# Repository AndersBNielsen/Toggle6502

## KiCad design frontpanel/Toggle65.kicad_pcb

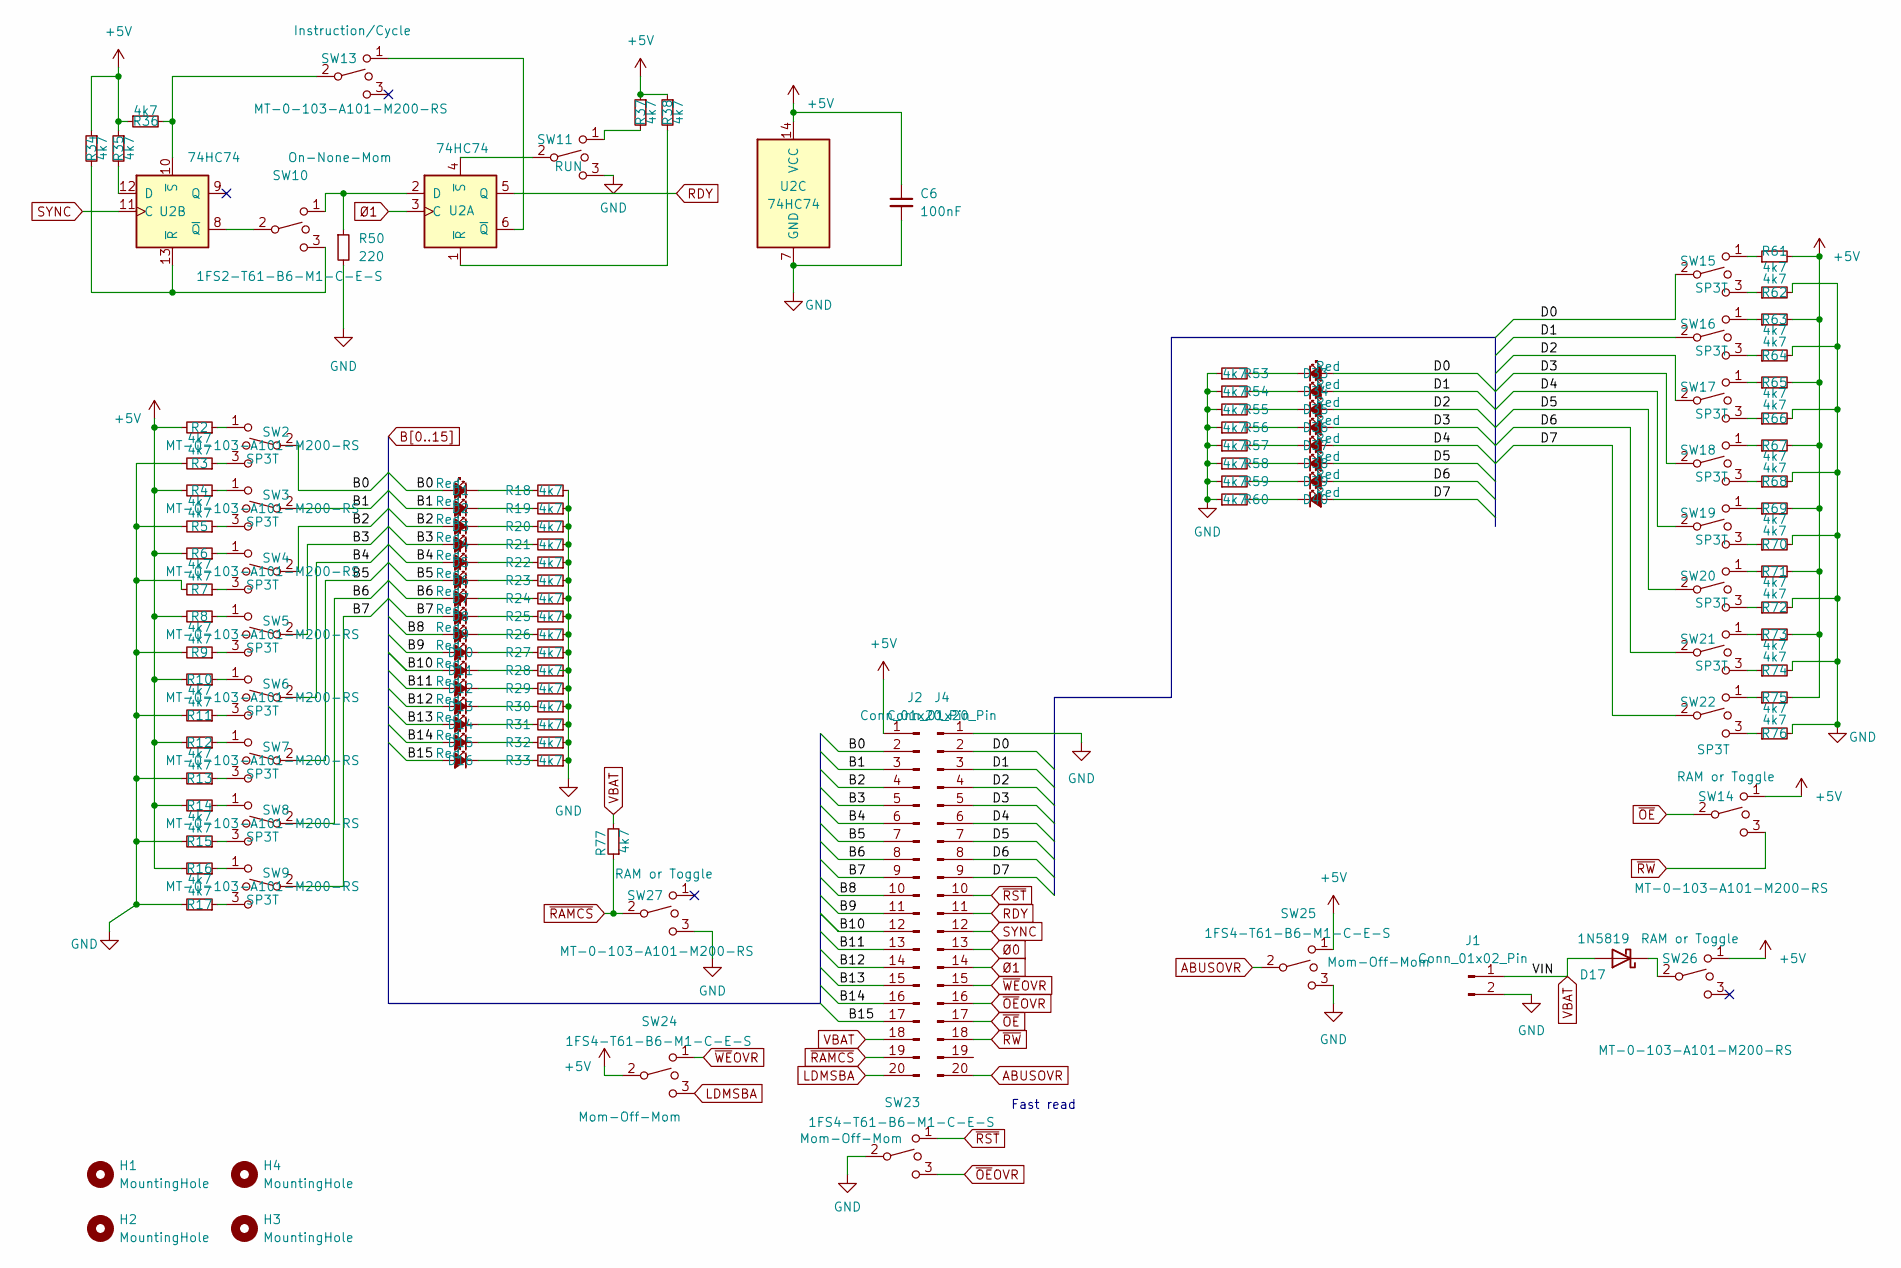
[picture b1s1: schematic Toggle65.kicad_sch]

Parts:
C6: 100nF; C_Disc_D5.0mm_W2.5mm_P5.00mm; LCSC C49678
D1, D2, D3, D4, D5, D6, D7, D8, D9, D10, D11, D12, D13, D14, D15, D16, D33, D34, D35, D36, D37, D38, D39, D40: Red; LED_D5.0mm
D17: 1N5819; D_DO-41_SOD81_P10.16mm_Horizontal
H1, H2, H3, H4: MountingHole; MountingHole_3.2mm_M3_DIN965
J1: Conn_01x02_Pin; PinHeader_1x02_P2.54mm_Vertical
J2, J4: Conn_01x20_Pin; PinHeader_1x20_P2.54mm_Vertical
R2, R3, R4, R5, R6, R7, R8, R9, R10, R11, R12, R13, R14, R15, R16, R17, R18, R19, R20, R21, R22, R23, R24, R25, R26, R27, R28, R29, R30, R31, R32, R33, R34, R35, R36, R37, R38, R53, R54, R55, R56, R57, R58, R59, R60, R61, R62, R63, R64, R65, R66, R67, R68, R69, R70, R71, R72, R73, R74, R75, R76, R77: 4k7; R_Axial_DIN0204_L3.6mm_D1.6mm_P5.08mm_Horizontal
R50: 220; R_Axial_DIN0204_L3.6mm_D1.6mm_P5.08mm_Horizontal
SW2, SW3, SW4, SW5, SW6, SW7, SW8, SW9, SW15, SW16, SW17, SW18, SW19, SW20, SW21, SW22: SP3T; SW_Toggle_Blue_wSlots; LCSC C1788493
SW10: On-None-Mom; SW_Toggle_Blue_wSlots
SW11: RUN; SW_Toggle_Blue_wSlots; LCSC C1788493
SW13: Instruction/Cycle; SW_Toggle_Blue_wSlots; LCSC C1788493
SW14, SW26, SW27: RAM or Toggle; SW_Toggle_Blue_wSlots; LCSC C1788493
SW23, SW24, SW25: Mom-Off-Mom; SW_Toggle_Blue_wSlots
U2: 74HC74; DIP-14_W7.62mm_Socket

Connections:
+5V: C6.1, J2.1, R2.2, R4.2, R6.2, R8.2, R10.2, R12.2, R14.2, R16.2, R34.1, R35.1, R36.1, R37.1, R38.1, R61.2, R63.2, R65.2, R67.2, R69.2, R71.2, R73.2, R75.2, SW14.1, SW24.2, SW25.1, SW26.1, U2.14 (VCC)
/D0: D33.2 (A), J4.2, SW15.2
/D1: D34.2 (A), J4.3, SW16.2
/D2: D35.2 (A), J4.4, SW17.2
/D3: D36.2 (A), J4.5, SW18.2
/D4: D37.2 (A), J4.6, SW19.2
/D5: D38.2 (A), J4.7, SW20.2
/D6: D39.2 (A), J4.8, SW21.2
/D7: D40.2 (A), J4.9, SW22.2
ABUSOVR: J4.20, SW25.2
B0: D1.2 (A), J2.2, SW2.2
B1: D2.2 (A), J2.3, SW3.2
B2: D3.2 (A), J2.4, SW4.2
B3: D4.2 (A), J2.5, SW5.2
B4: D5.2 (A), J2.6, SW6.2
B5: D6.2 (A), J2.7, SW7.2
B6: D7.2 (A), J2.8, SW8.2
B7: D8.2 (A), J2.9, SW9.2
B8: D9.2 (A), J2.10
B9: D10.2 (A), J2.11
B10: D11.2 (A), J2.12
B11: D12.2 (A), J2.13
B12: D13.2 (A), J2.14
B13: D14.2 (A), J2.15
B14: D15.2 (A), J2.16
B15: D16.2 (A), J2.17
GND: C6.2, J1.2, J4.1, R3.2, R5.2, R7.2, R9.2, R11.2, R13.2, R15.2, R17.2, R18.1, R19.1, R20.1, R21.1, R22.1, R23.1, R24.1, R25.1, R26.1, R27.1, R28.1, R29.1, R30.1, R31.1, R32.1, R33.1, R50.2, R53.1, R54.1, R55.1, R56.1, R57.1, R58.1, R59.1, R60.1, R62.2, R64.2, R66.2, R68.2, R70.2, R72.2, R74.2, R76.2, SW11.3, SW23.2, SW25.3, SW27.3, U2.7 (GND)
LDMSBA: J2.20, SW24.3
unnamed: D1.1 (K), R18.2
unnamed: D2.1 (K), R19.2
unnamed: D3.1 (K), R20.2
unnamed: D4.1 (K), R21.2
unnamed: D5.1 (K), R22.2
unnamed: D6.1 (K), R23.2
unnamed: D7.1 (K), R24.2
unnamed: D8.1 (K), R25.2
unnamed: D9.1 (K), R26.2
unnamed: D10.1 (K), R27.2
unnamed: D11.1 (K), R28.2
unnamed: D12.1 (K), R29.2
unnamed: D13.1 (K), R30.2
unnamed: D14.1 (K), R31.2
unnamed: D15.1 (K), R32.2
unnamed: D16.1 (K), R33.2
unnamed: D17.1 (K), SW26.2
unnamed: D33.1 (K), R53.2
unnamed: D34.1 (K), R54.2
unnamed: D35.1 (K), R55.2
unnamed: D36.1 (K), R56.2
unnamed: D37.1 (K), R57.2
unnamed: D38.1 (K), R58.2
unnamed: D39.1 (K), R59.2
unnamed: D40.1 (K), R60.2
unnamed: R2.1, SW2.1
unnamed: R3.1, SW2.3
unnamed: R4.1, SW3.1
unnamed: R5.1, SW3.3
unnamed: R6.1, SW4.1
unnamed: R7.1, SW4.3
unnamed: R8.1, SW5.1
unnamed: R9.1, SW5.3
unnamed: R10.1, SW6.1
unnamed: R11.1, SW6.3
unnamed: R12.1, SW7.1
unnamed: R13.1, SW7.3
unnamed: R14.1, SW8.1
unnamed: R15.1, SW8.3
unnamed: R16.1, SW9.1
unnamed: R17.1, SW9.3
unnamed: R37.2, SW11.1
unnamed: R61.1, SW15.1
unnamed: R62.1, SW15.3
unnamed: R63.1, SW16.1
unnamed: R64.1, SW16.3
unnamed: R65.1, SW17.1
unnamed: R66.1, SW17.3
unnamed: R67.1, SW18.1
unnamed: R68.1, SW18.3
unnamed: R69.1, SW19.1
unnamed: R70.1, SW19.3
unnamed: R71.1, SW20.1
unnamed: R72.1, SW20.3
unnamed: R73.1, SW21.1
unnamed: R74.1, SW21.3
unnamed: R75.1, SW22.1
unnamed: R76.1, SW22.3
unnamed: R50.1, SW10.1, U2.2 (D)
unnamed: SW13.1, U2.6 (~Q)
unnamed: R38.2, U2.1 (~R)
unnamed: SW11.2, U2.4 (~S)
unnamed: R35.2, U2.12 (D)
unnamed: SW10.2, U2.8 (~Q)
unnamed: R34.2, SW10.3, U2.13 (~R)
unnamed: R36.2, SW13.2, U2.10 (~S)
RDY: J4.11, U2.5 (Q)
SYNC: J4.12, U2.11 (C)
VBAT: D17.2 (A), J1.1, J2.18, R77.2
~OE: J4.17, SW14.2
~OEOVR: J4.16, SW23.3
~RAMCS: J2.19, R77.1, SW27.2
~RST: J4.10, SW23.1
~RW: J4.18, SW14.3
~WEOVR: J4.15, SW24.1
Ø0: J4.13
Ø1: J4.14, U2.3 (C)

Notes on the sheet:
Fast read

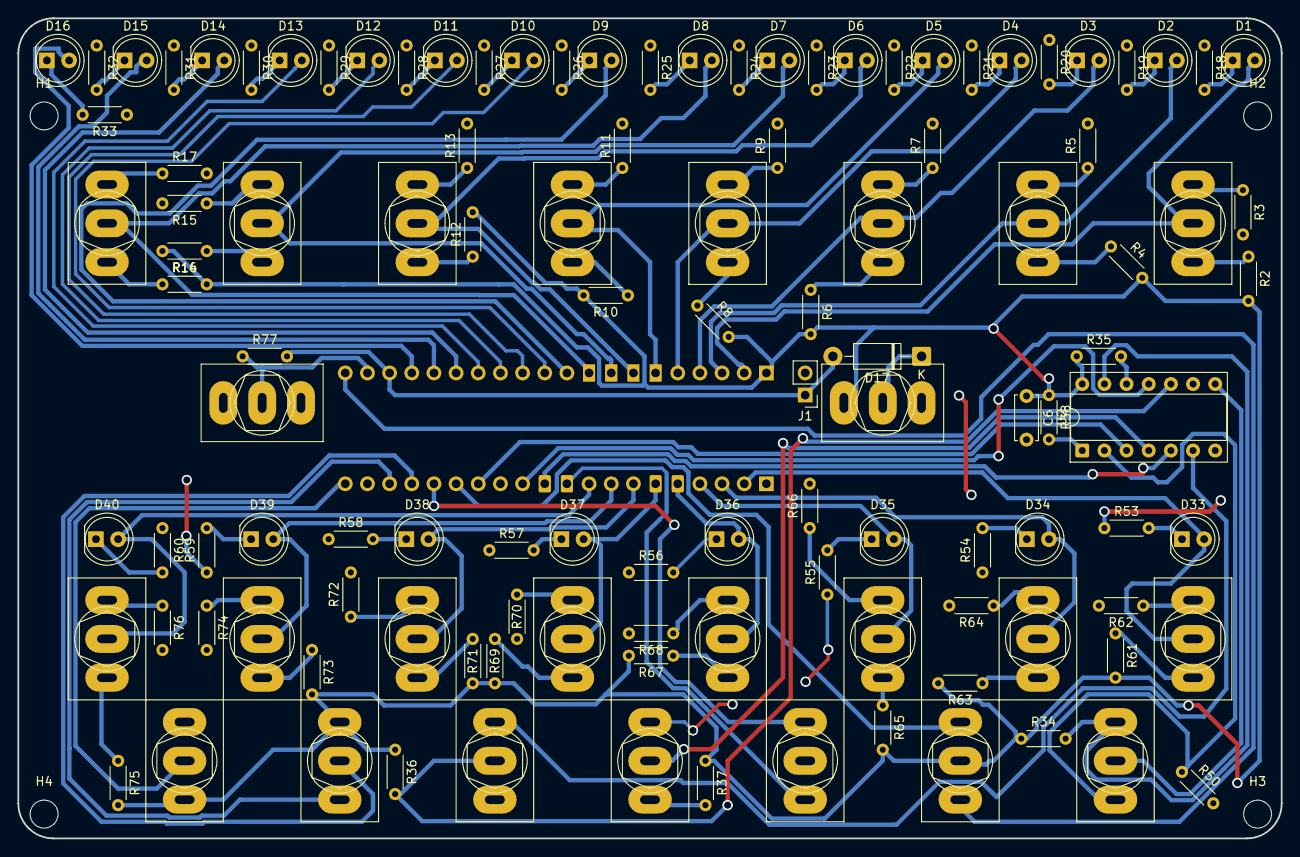
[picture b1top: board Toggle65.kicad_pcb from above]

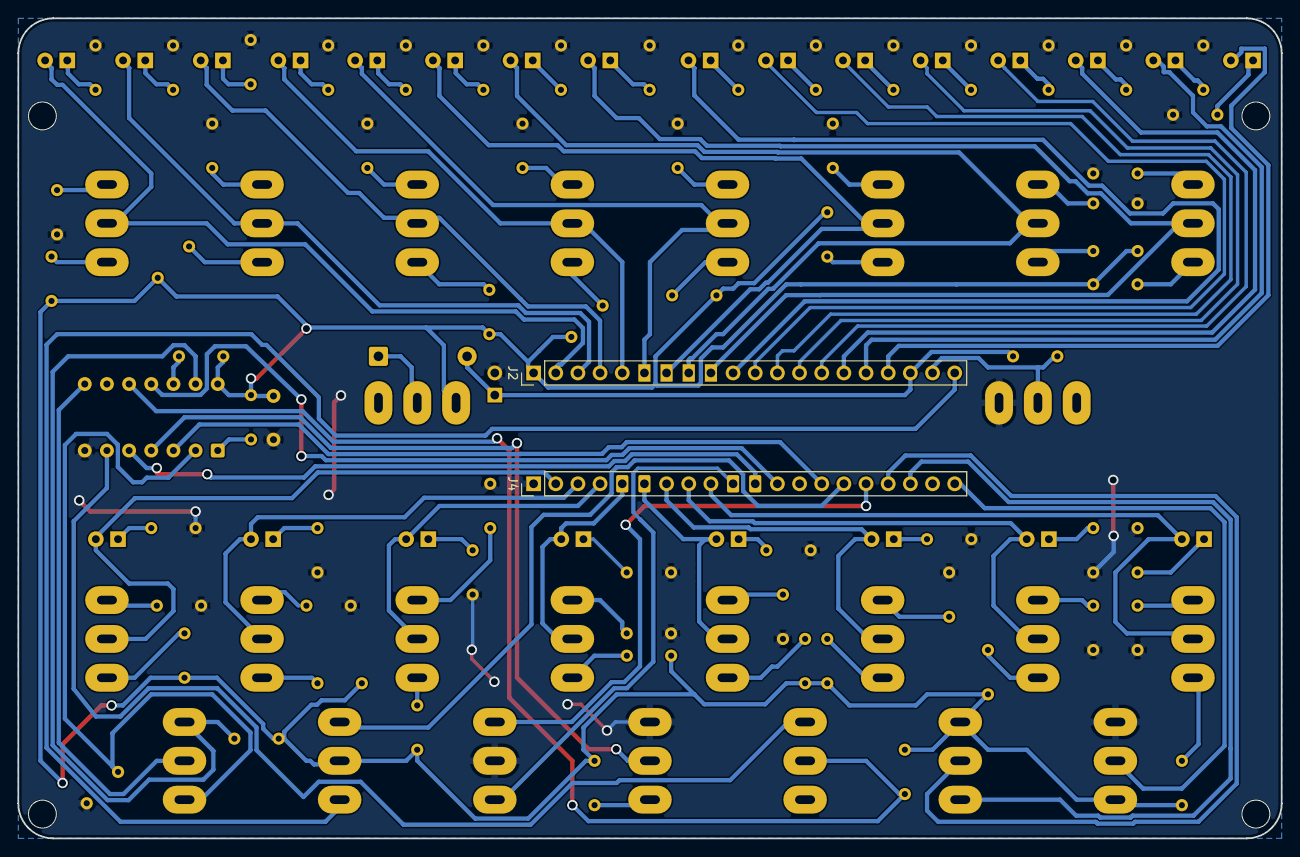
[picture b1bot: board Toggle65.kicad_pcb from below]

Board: 2 copper layers, 144.8 x 94.0 mm, 122 parts (2 on the bottom side), 104 nets.

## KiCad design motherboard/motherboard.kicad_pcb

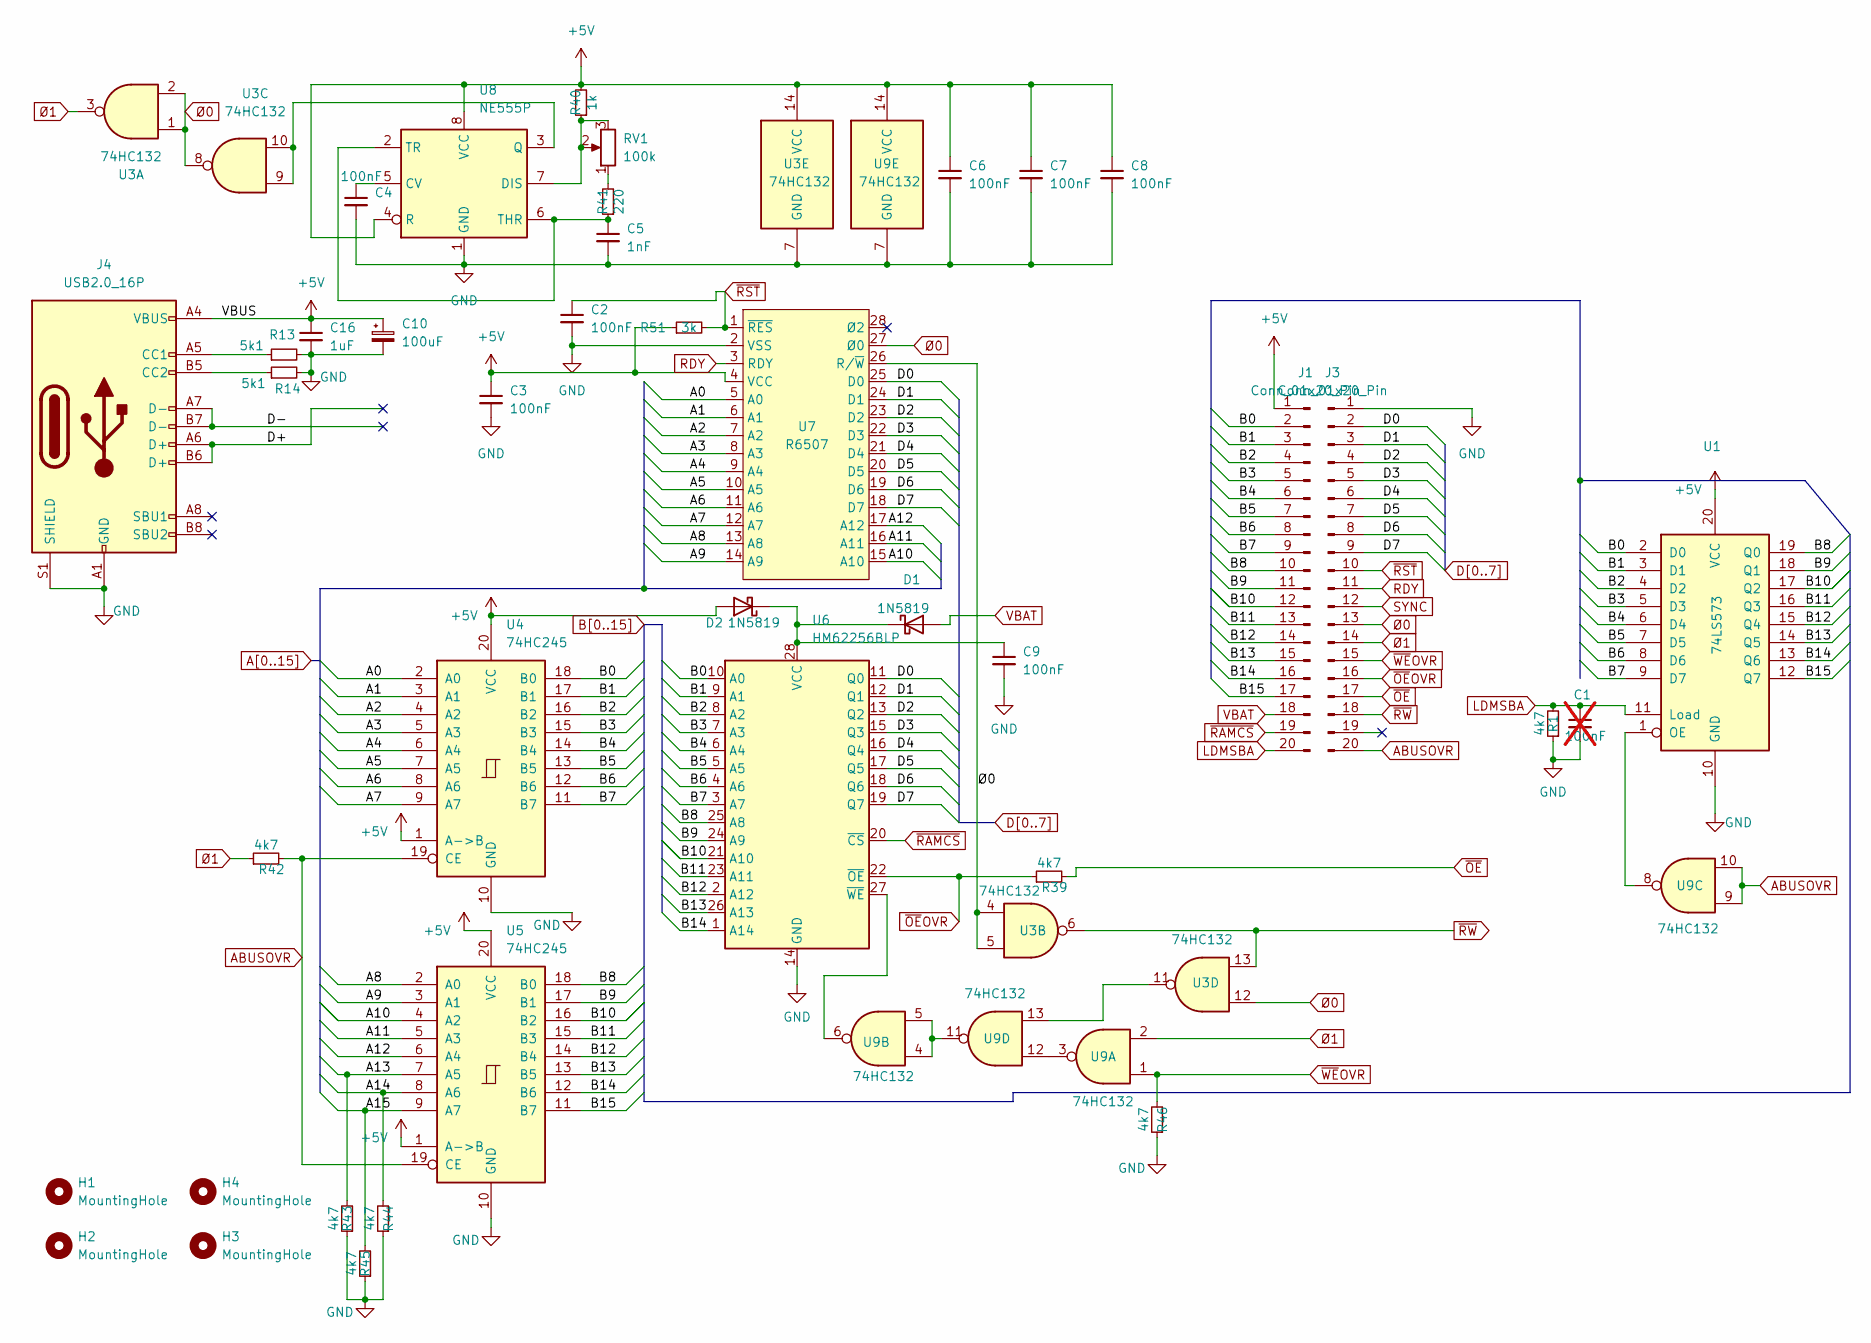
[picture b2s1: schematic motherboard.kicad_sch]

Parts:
C1: 100nF; C_Disc_D5.0mm_W2.5mm_P5.00mm; LCSC C49678; not fitted
C2, C3, C4, C6, C7, C8, C9: 100nF; C_Disc_D5.0mm_W2.5mm_P5.00mm; LCSC C49678
C5: 1nF; C_Disc_D5.0mm_W2.5mm_P5.00mm; LCSC C49678
C10: 100uF; CP_Radial_D5.0mm_P2.00mm
C16: 1uF; C_0805_2012Metric; LCSC C28323
D1, D2: 1N5819; D_DO-41_SOD81_P10.16mm_Horizontal
H1, H2, H3, H4: MountingHole; MountingHole_3.2mm_M3_DIN965
J1, J3: Conn_01x20_Pin; PinHeader_1x20_P2.54mm_Vertical
J4: USB2.0_16P; USB_C_Receptacle_HCTL_HC-TYPE-C-16P-01A; LCSC C2894897
R1, R39, R42, R43, R44, R45, R46: 4k7; R_Axial_DIN0204_L3.6mm_D1.6mm_P5.08mm_Horizontal
R13, R14: 5k1; R_0805_2012Metric
R40: 1k; R_Axial_DIN0204_L3.6mm_D1.6mm_P5.08mm_Horizontal
R41: 220; R_Axial_DIN0204_L3.6mm_D1.6mm_P5.08mm_Horizontal
R51: 3k; R_Axial_DIN0204_L3.6mm_D1.6mm_P5.08mm_Horizontal; LCSC C17661
RV1: 100k; Potentiometer_Alps_RK09Y11_Single_Horizontal
U1: 74LS573; DIP-20_W7.62mm_Socket
U3, U9: 74HC132; DIP-14_W7.62mm_Socket
U4, U5: 74HC245; DIP-20_W7.62mm_Socket
U6: HM62256BLP; DIP-28_W15.24mm
U7: R6507; DIP-28_W15.24mm
U8: NE555P; DIP-8_W7.62mm

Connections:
+5V: C3.1, C6.1, C7.1, C8.1, C10.1, C16.1, D2.2 (A), J1.1, J4.A4 (VBUS), J4.A9 (VBUS), J4.B4 (VBUS), J4.B9 (VBUS), R40.2, R51.1, U1.20 (VCC), U3.14 (VCC), U4.1 (A->B), U4.20 (VCC), U5.1 (A->B), U5.20 (VCC), U7.4 (VCC), U8.4 (R), U8.8 (VCC), U9.14 (VCC)
/D+: J4.A6 (D+), J4.B6 (D+)
/D-: J4.A7 (D-), J4.B7 (D-)
A0: U4.2 (A0), U7.5 (A0)
A1: U4.3 (A1), U7.6 (A1)
A2: U4.4 (A2), U7.7 (A2)
A3: U4.5 (A3), U7.8 (A3)
A4: U4.6 (A4), U7.9 (A4)
A5: U4.7 (A5), U7.10 (A5)
A6: U4.8 (A6), U7.11 (A6)
A7: U4.9 (A7), U7.12 (A7)
A8: U5.2 (A0), U7.13 (A8)
A9: U5.3 (A1), U7.14 (A9)
A10: U5.4 (A2), U7.15 (A10)
A11: U5.5 (A3), U7.16 (A11)
A12: U5.6 (A4), U7.17 (A12)
A13: R43.2, U5.7 (A5)
A14: R44.2, U5.8 (A6)
A15: R45.2, U5.9 (A7)
ABUSOVR: J3.20, R42.2, U4.19 (CE), U5.19 (CE), U9.9, U9.10
B0: J1.2, U1.2 (D0), U4.18 (B0), U6.10 (A0)
B1: J1.3, U1.3 (D1), U4.17 (B1), U6.9 (A1)
B2: J1.4, U1.4 (D2), U4.16 (B2), U6.8 (A2)
B3: J1.5, U1.5 (D3), U4.15 (B3), U6.7 (A3)
B4: J1.6, U1.6 (D4), U4.14 (B4), U6.6 (A4)
B5: J1.7, U1.7 (D5), U4.13 (B5), U6.5 (A5)
B6: J1.8, U1.8 (D6), U4.12 (B6), U6.4 (A6)
B7: J1.9, U1.9 (D7), U4.11 (B7), U6.3 (A7)
B8: J1.10, U1.19 (Q0), U5.18 (B0), U6.25 (A8)
B9: J1.11, U1.18 (Q1), U5.17 (B1), U6.24 (A9)
B10: J1.12, U1.17 (Q2), U5.16 (B2), U6.21 (A10)
B11: J1.13, U1.16 (Q3), U5.15 (B3), U6.23 (A11)
B12: J1.14, U1.15 (Q4), U5.14 (B4), U6.2 (A12)
B13: J1.15, U1.14 (Q5), U5.13 (B5), U6.26 (A13)
B14: J1.16, U1.13 (Q6), U5.12 (B6), U6.1 (A14)
B15: J1.17, U1.12 (Q7), U5.11 (B7)
D0: J3.2, U6.11 (Q0), U7.25 (D0)
D1: J3.3, U6.12 (Q1), U7.24 (D1)
D2: J3.4, U6.13 (Q2), U7.23 (D2)
D3: J3.5, U6.15 (Q3), U7.22 (D3)
D4: J3.6, U6.16 (Q4), U7.21 (D4)
D5: J3.7, U6.17 (Q5), U7.20 (D5)
D6: J3.8, U6.18 (Q6), U7.19 (D6)
D7: J3.9, U6.19 (Q7), U7.18 (D7)
GND: C1.2, C2.2, C3.2, C4.2, C5.2, C6.2, C7.2, C8.2, C9.2, C10.2, C16.2, J3.1, J4.A1 (GND), J4.A12 (GND), J4.B1 (GND), J4.B12 (GND), J4.S1 (SHIELD), R1.1, R13.2, R14.2, R43.1, R44.1, R45.1, R46.1, U1.10 (GND), U3.7 (GND), U4.10 (GND), U5.10 (GND), U6.14 (GND), U7.2 (VSS), U8.1 (GND), U9.7 (GND)
LDMSBA: C1.1, J1.20, R1.2, U1.11 (Load)
unnamed: C9.1, D1.1 (K), D2.1 (K), U6.28 (VCC)
unnamed: J4.A5 (CC1), R13.1
unnamed: J4.B5 (CC2), R14.1
unnamed: R41.2, RV1.1
unnamed: U1.1 (OE), U9.8
unnamed: U3.11, U9.13
unnamed: U6.27 (~WE), U9.6
unnamed: C4.1, U8.5 (CV)
unnamed: R40.1, RV1.2, RV1.3, U8.7 (DIS)
unnamed: U3.9, U3.10, U8.3 (Q)
unnamed: C5.1, R41.1, U8.2 (TR), U8.6 (THR)
unnamed: U9.4, U9.5, U9.11
unnamed: U9.3, U9.12
RDY: J3.11, U7.3 (RDY)
SYNC: J3.12
VBAT: D1.2 (A), J1.18
~OE: J3.17, R39.2
~OEOVR: J3.16, R39.1, U6.22 (~OE)
~RAMCS: J1.19, U6.20 (~CS)
~RST: C2.1, J3.10, R51.2, U7.1 (~RES)
~RW: J3.18, U3.6, U3.13
~WEOVR: J3.15, R46.2, U9.1
Ø0: J3.13, U3.1, U3.2, U3.4, U3.5, U3.8, U3.12, U7.26 (R/~W), U7.27 (Ø0)
Ø1: J3.14, R42.1, U3.3, U9.2

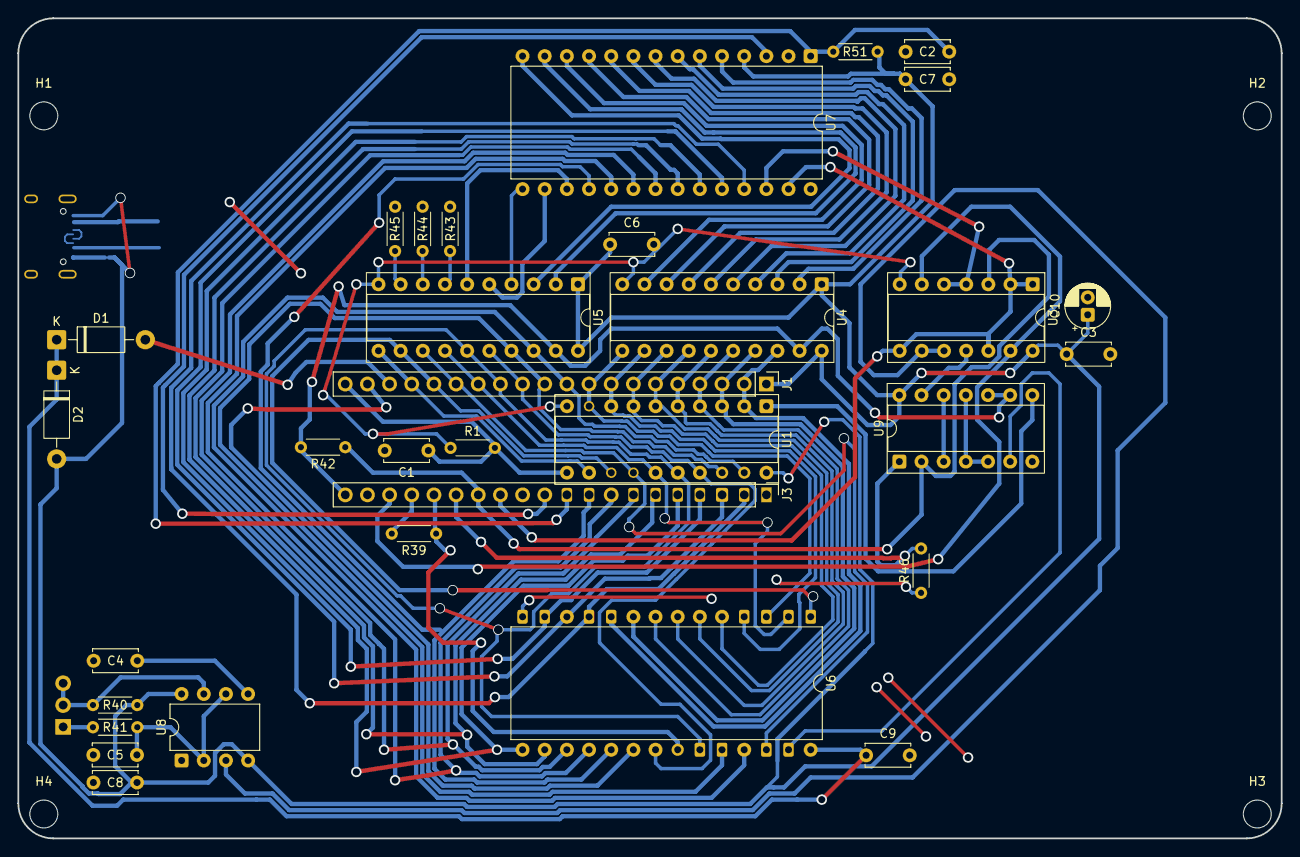
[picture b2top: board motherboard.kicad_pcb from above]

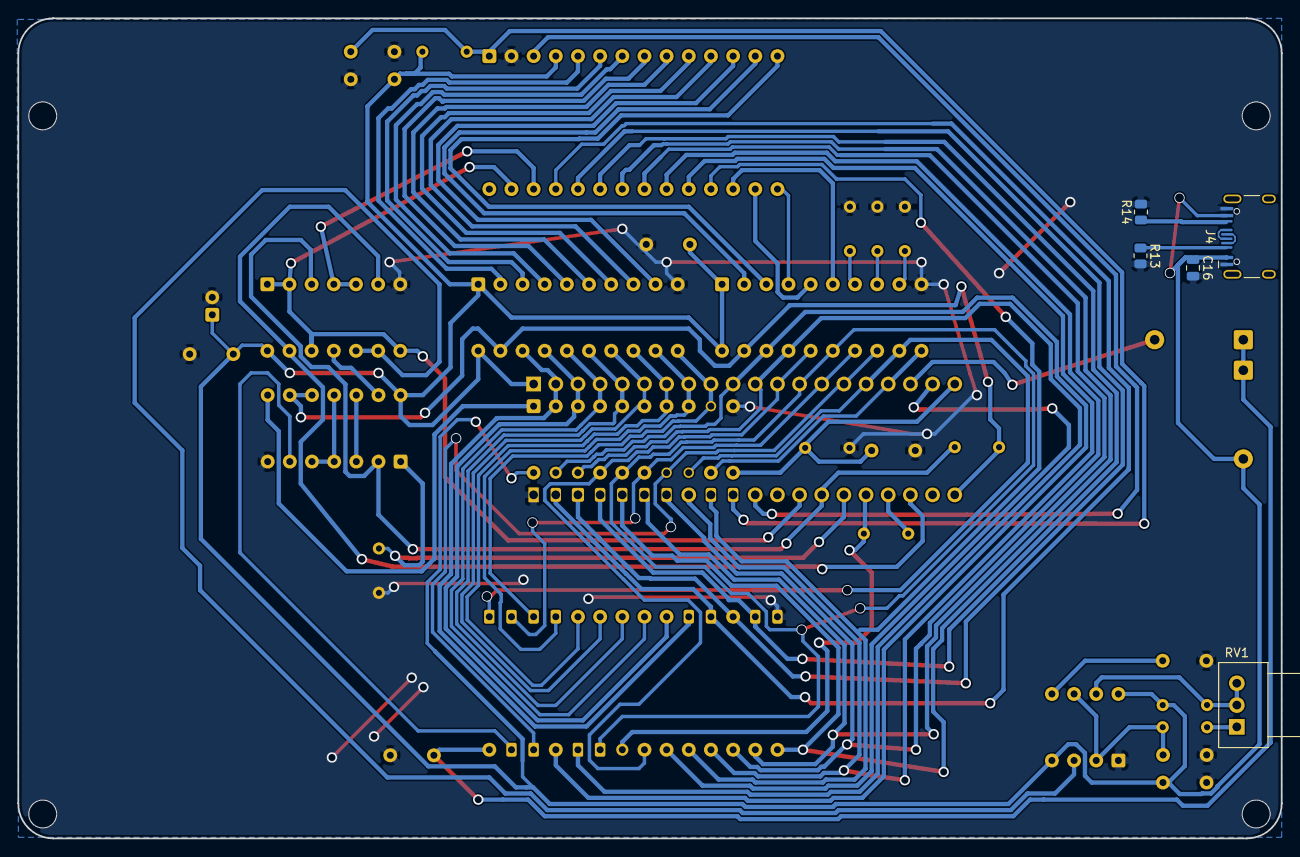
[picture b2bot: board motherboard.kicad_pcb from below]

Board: 2 copper layers, 144.8 x 94.0 mm, 41 parts (5 on the bottom side), 69 nets.
